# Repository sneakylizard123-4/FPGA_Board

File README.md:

# FPGA_Board

A iCE40 FPGA devboard

## Custom Features
- ICE40UP5K-SG48ITR FPGA (5280 LUTs, QFN-48)
- On-board FT232H flasher with EEPROM
- 16MB W25Q128JVS SPI flash
- USB-C with ESD protection
- RGB LED, green config-status LED, reset button
- 12MHz oscillator, 4-layer PCB

## PCB Design

The board is a 4-layer PCB.

It is built around the Lattice iCE40 FPGA, designed to be programmed over USB through the on-board FT232H. The SPI flash boots the bitstream on power-up.
It is fully supported by the open-source yosys/nextpnr/icestorm flow.

## Firmware

As the board uses an iCE40 UltraPlus, it is programmed with yosys + nextpnr-ice40 + icepack + iceprog/icestorm.

## BOM

| Ref | Value | LCSC # | MPN | Manufacturer | Footprint | Qty | Unit $ | Ext $ | Link |
|-----|-------|--------|-----|--------------|-----------|-----|--------|-------|------|
| C1,C2,C3,C4,C5,C12,C13,C14,C17,C24,C34,C35 | 10uF 0402 | C307415 | - | - | 0402 | 12 | 0.1900 | 2.28 | [LCSC](https://www.lcsc.com/product-detail/C307415.html) |
| C6,C7,C8,C9,C10,C11,C15,C16,C18,C19,C20,C21,C22,C23,C25,C26,C27,C28,C29,C30,C31,C32,C33,C37,C38 | 100nF 0402 | C131394 | - | - | 0402 | 25 | 0.0096 | 0.24 | [LCSC](https://www.lcsc.com/product-detail/C131394.html) |
| C36 | 4.7uF 0402 | C21120 | - | - | 0402 | 1 | 0.0200 | 0.02 | [LCSC](https://www.lcsc.com/product-detail/C21120.html) |
| D1 | LED_ARGB PLCC4 | C2786 | - | - | LED_Cree-PLCC4_2x2mm_CW | 1 | 0.1300 | 0.13 | [LCSC](https://www.lcsc.com/product-detail/C2786.html) |
| D2 | Green LED 0402 | C2286 | - | - | 0402 | 1 | 0.0100 | 0.01 | [LCSC](https://www.lcsc.com/product-detail/C2286.html) |
| FB1,FB2,FB3 | Ferrite Bead 1.5k | C82155 | BLM18HE152SN1D | muRata | 0603 | 3 | 0.0300 | 0.09 | [LCSC](https://www.lcsc.com/product-detail/C82155.html) |
| J1 | USB-C Receptacle 14P | C165948 | TYPE-C-31-M-12 | Korean Hroparts Elec | USB-C | 1 | 0.1900 | 0.19 | [LCSC](https://www.lcsc.com/product-detail/C165948.html) |
| J3,J4 | Pin Header 2x12 2.54mm | C492423 | PZ254V-12-12P | XFCN | Through Hole | 2 | 0.0700 | 0.14 | [LCSC](https://www.lcsc.com/product-detail/C492423.html) |
| R1,R2 | 5.1k 1% 0402 | C25905 | 0402WGF5101TCE | UNI-ROYAL | 0402 | 2 | 0.0040 | 0.01 | [LCSC](https://www.lcsc.com/product-detail/C25905.html) |
| R3,R4 | 22R 1% 0402 | C23200 | - | - | 0402 | 2 | 0.0040 | 0.01 | [LCSC](https://www.lcsc.com/product-detail/C23200.html) |
| R5,R6,R10,R11,R19,R20,R21,R23,R24 | 10k 1% 0402 | C25904 | - | - | 0402 | 9 | 0.0040 | 0.04 | [LCSC](https://www.lcsc.com/product-detail/C25904.html) |
| R7 | 1k 1% 0402 | C25898 | - | - | 0402 | 1 | 0.0040 | 0.00 | [LCSC](https://www.lcsc.com/product-detail/C25898.html) |
| R8,R9,R14 | 0R 0402 | C25887 | - | - | 0402 | 3 | 0.0030 | 0.01 | [LCSC](https://www.lcsc.com/product-detail/C25887.html) |
| R12 | 100R 1% 0402 | C22861 | - | - | 0402 | 1 | 0.0040 | 0.00 | [LCSC](https://www.lcsc.com/product-detail/C22861.html) |
| R18 | 12k 1% 0402 | C25913 | - | - | 0402 | 1 | 0.0040 | 0.00 | [LCSC](https://www.lcsc.com/product-detail/C25913.html) |
| R22 | 2.2k 1% 0402 | C25901 | - | - | 0402 | 1 | 0.0040 | 0.00 | [LCSC](https://www.lcsc.com/product-detail/C25901.html) |
| SW1 | Tactile Switch EVQPUD | C158289 | EVQPUM | PANASONIC | SMD | 1 | 0.2000 | 0.20 | [LCSC](https://www.lcsc.com/product-detail/C158289.html) |
| U1 | USBLC6-2SC6 | C7519 | USBLC6-2SC6 | ST | SOT-23-6 | 1 | 0.1800 | 0.18 | [LCSC](https://www.lcsc.com/product-detail/C7519.html) |
| U2 | TLV75712PDBV | C485515 | TLV75712PDBVR | TI | SOT-23-5 | 1 | 0.1800 | 0.18 | [LCSC](https://www.lcsc.com/product-detail/C485515.html) |
| U3 | TLV75725PDBV | C485516 | TLV75725PDBVR | TI | SOT-23-5 | 1 | 0.1800 | 0.18 | [LCSC](https://www.lcsc.com/product-detail/C485516.html) |
| U4 | TLV75733PDBV | C485517 | TLV75733PDBVR | TI | SOT-23-5 | 1 | 0.1800 | 0.18 | [LCSC](https://www.lcsc.com/product-detail/C485517.html) |
| U5 | 74AUC2G240 | C2652105 | - | - | VSSOP-8 | 1 | 0.7200 | 0.72 | [LCSC](https://www.lcsc.com/product-detail/C2652105.html) |
| U6 | ICE40UP5K-SG48ITR | C2678152 | ICE40UP5K-SG48ITR | Lattice | QFN-48 | 1 | 8.5600 | 8.56 | [LCSC](https://www.lcsc.com/product-detail/C2678152.html) |
| U7 | W25Q128JVS | C113767 | W25Q128JVS | Winbond | SOIC-8 | 1 | 2.5200 | 2.52 | [LCSC](https://www.lcsc.com/product-detail/C113767.html) |
| U8 | FT232H | C51997 | FT232HL | FTDI | LQFP-48 | 1 | 10.6200 | 10.62 | [LCSC](https://www.lcsc.com/product-detail/C51997.html) |
| U9 | 93LC56BT-I/OT | C190271 | 93LC56BT-I/OT | Microchip | SOIC-8 | 1 | 0.4500 | 0.45 | [LCSC](https://www.lcsc.com/product-detail/C190271.html) |
| Y1 | SG-210STF 12MHz | C17426037 | SG-210STF | Seiko Epson | 2.5x2.0mm | 1 | 0.3700 | 0.37 | [LCSC](https://www.lcsc.com/product-detail/C17426037.html) |
| PCB | Bare PCB | — | — | — | 50x70mm | 1 | 20.0000 | 20.00 | — |
| STENCIL | Top stencil | — | — | — | 100x150mm | 1 | 18.0000 | 18.00 | — |
| **Total** | — | — | — | — | — | **79** | — | **65.33** | — |

Full CSVs: [LCSC BOM](BOM.csv)
[KiCad generated BOM](kicad/production/bom.csv)
[Pick and place](kicad/production/positions.csv)

## Production

Production files in [Prod Files](kicad/production/)
This board assumes JLCPCB's standard 4 layer
- HASL Lead Free
- 1.6mm thick board

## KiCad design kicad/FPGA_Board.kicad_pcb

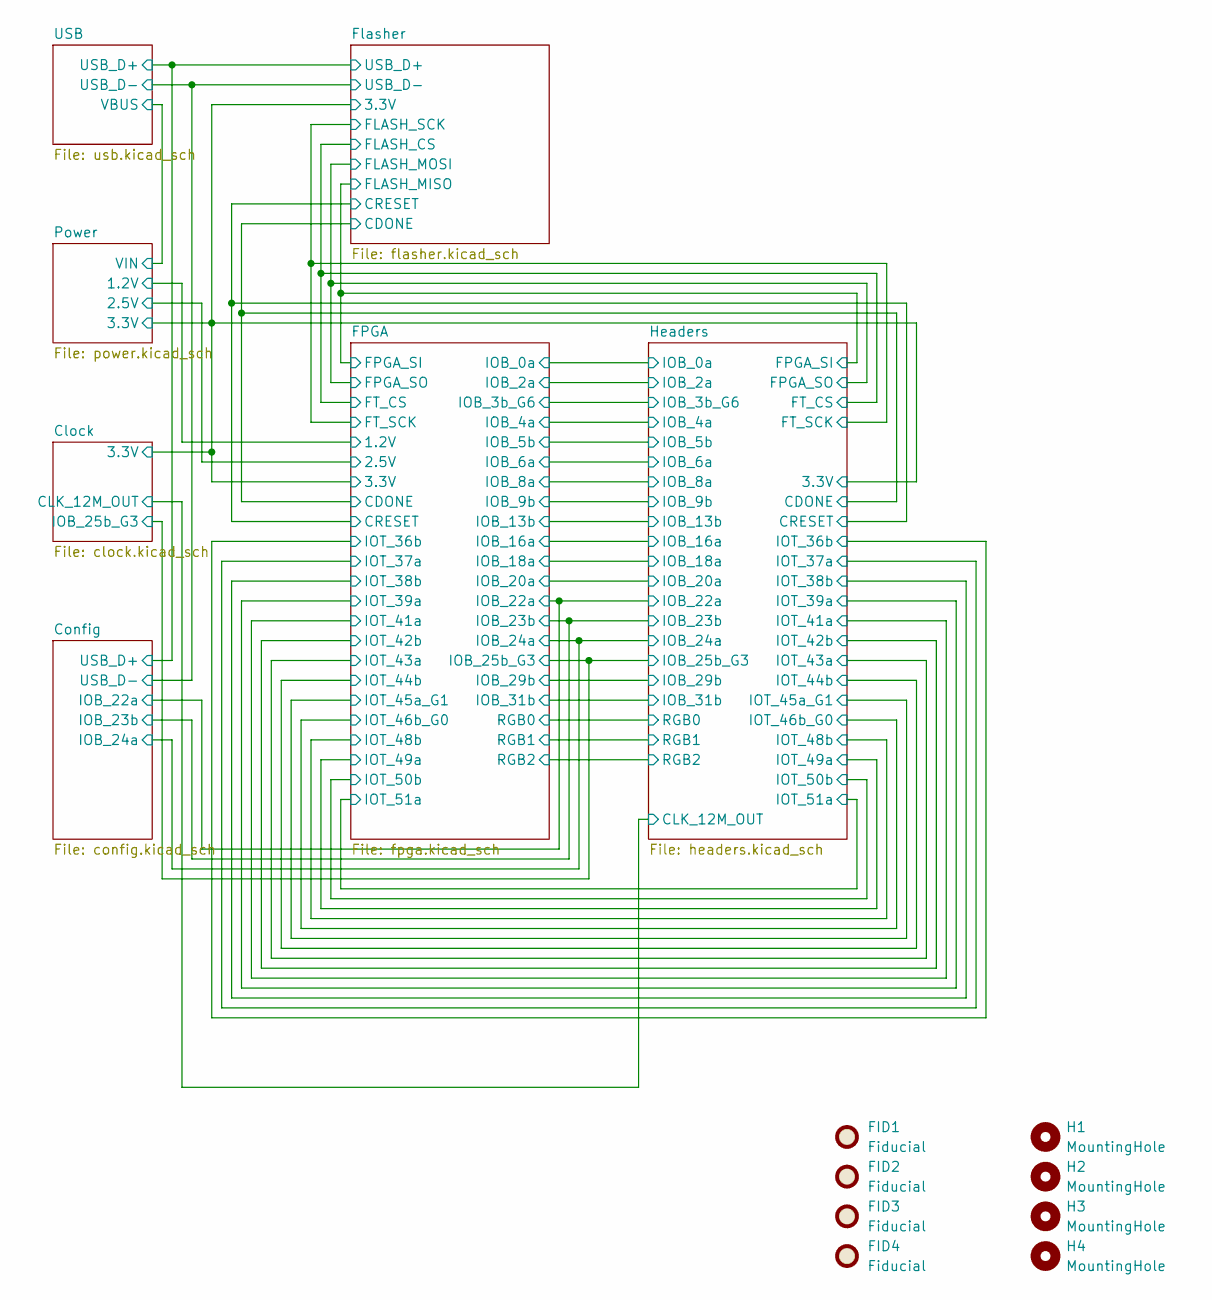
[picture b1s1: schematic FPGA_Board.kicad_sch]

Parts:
FID1, FID2, FID3, FID4: Fiducial; Fiducial_0.5mm_Mask1mm
H1, H2, H3, H4: MountingHole; MountingHole_3.2mm_M3

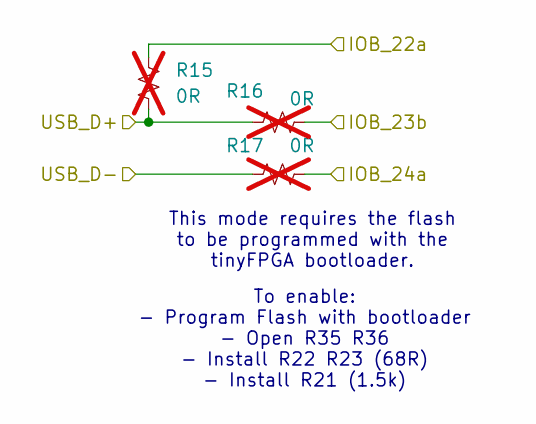
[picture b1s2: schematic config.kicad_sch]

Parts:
R15, R16, R17: 0R; R_0402_1005Metric; not fitted

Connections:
/Config/IOB_22a: R15.2; also elsewhere on the board
/Config/IOB_23b: R16.2; also elsewhere on the board
/Config/IOB_24a: R17.2; also elsewhere on the board
/Config/USB_D+: R15.1, R16.1; also elsewhere on the board
/Config/USB_D-: R17.1; also elsewhere on the board

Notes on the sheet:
This mode requires the flash to be programmed with the tinyFPGA bootloader.
To enable: - Program Flash with bootloader - Open R35 R36 - Install R22 R23 (68R) - Install R21 (1.5k)

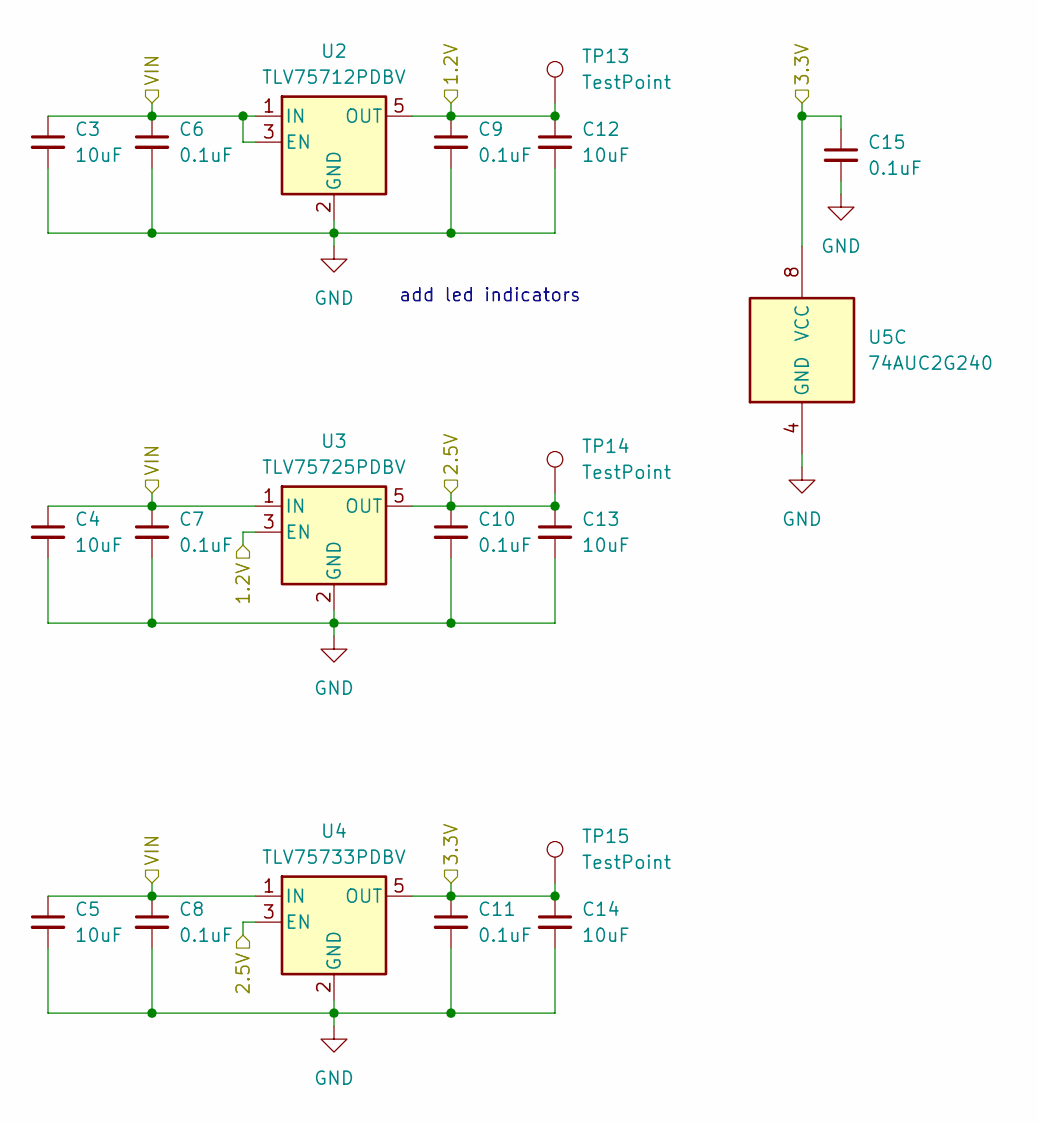
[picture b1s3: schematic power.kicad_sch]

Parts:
C3, C4, C5, C12, C13, C14: 10uF; C_0402_1005Metric
C6, C7, C8, C9, C10, C11, C15: 0.1uF; C_0402_1005Metric
TP13, TP14, TP15: TestPoint; TestPoint_Pad_2.0x2.0mm
U2: TLV75712PDBV; SOT-23-5
U3: TLV75725PDBV; SOT-23-5
U4: TLV75733PDBV; SOT-23-5
U5: 74AUC2G240; VSSOP-8_3x3mm_P0.65mm

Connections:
/FPGA/1.2V: C9.1, C12.1, TP13.1 (1_1), U2.5 (OUT), U3.3 (EN); also elsewhere on the board
/FPGA/2.5V: C10.1, C13.1, TP14.1 (1_1), U3.5 (OUT), U4.3 (EN); also elsewhere on the board
/Flasher/3.3V: C11.1, C14.1, C15.1, TP15.1 (1_1), U4.5 (OUT), U5.8 (VCC); also elsewhere on the board
/Power/VIN: C3.1, C4.1, C5.1, C6.1, C7.1, C8.1, U2.1 (IN), U2.3 (EN), U3.1 (IN), U4.1 (IN); also elsewhere on the board
GND: C3.2, C4.2, C5.2, C6.2, C7.2, C8.2, C9.2, C10.2, C11.2, C12.2, C13.2, C14.2, C15.2, U2.2 (GND), U3.2 (GND), U4.2 (GND), U5.4 (GND); also elsewhere on the board

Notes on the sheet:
add led indicators

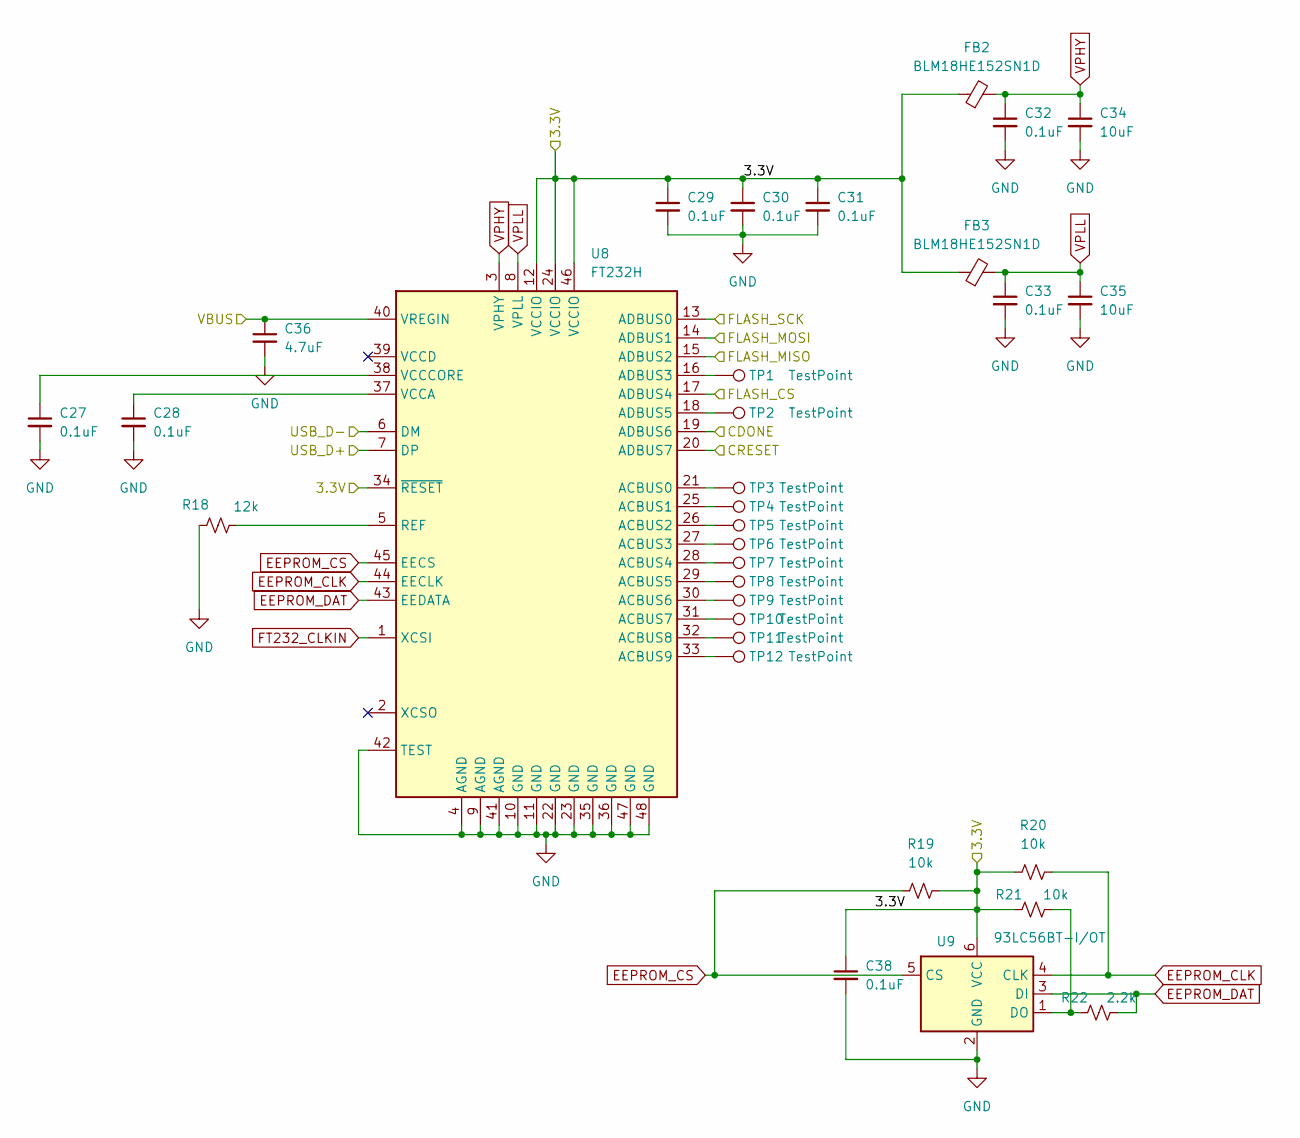
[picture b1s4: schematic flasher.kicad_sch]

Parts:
C27, C28, C29, C30, C31, C32, C33, C38: 0.1uF; C_0402_1005Metric
C34, C35: 10uF; C_0402_1005Metric
C36: 4.7uF; C_0402_1005Metric
FB2, FB3: BLM18HE152SN1D; L_0603_1608Metric
R18: 12k; R_0402_1005Metric
R19, R20, R21: 10k; R_0402_1005Metric
R22: 2.2k; R_0402_1005Metric
TP1, TP2, TP3, TP4, TP5, TP6, TP7, TP8, TP9, TP10, TP11, TP12: TestPoint; TestPoint_Pad_1.0x1.0mm
U8: FT232H; LQFP-48_7x7mm_P0.5mm
U9: 93LC56BT-I/OT; SOIC-8_3.9x4.9mm_P1.27mm

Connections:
/Config/USB_D+: U8.7 (DP); also elsewhere on the board
/Config/USB_D-: U8.6 (DM); also elsewhere on the board
/FPGA/CDONE: U8.19 (ADBUS6); also elsewhere on the board
/FPGA/CRESET: U8.20 (ADBUS7); also elsewhere on the board
/FPGA/FPGA_SI: U8.15 (ADBUS2); also elsewhere on the board
/FPGA/FPGA_SO: U8.14 (ADBUS1); also elsewhere on the board
/FPGA/FT_CS: U8.17 (ADBUS4); also elsewhere on the board
/FPGA/FT_SCK: U8.13 (ADBUS0); also elsewhere on the board
/Flasher/3.3V: C29.1, C30.1, C31.1, C38.1, FB2.1, FB3.1, R19.2, R20.1, R21.1, U8.12 (VCCIO), U8.24 (VCCIO), U8.34 (~RESET), U8.46 (VCCIO), U9.6 (VCC); also elsewhere on the board
/Flasher/VBUS: C36.1, U8.40 (VREGIN)
EEPROM_CLK: R20.2, U8.44 (EECLK), U9.4 (CLK)
EEPROM_CS: R19.1, U8.45 (EECS), U9.5 (CS)
EEPROM_DAT: R22.2, U8.43 (EEDATA), U9.3 (DI)
FT232_CLKIN: U8.1 (XCSI); also elsewhere on the board
GND: C27.2, C28.2, C29.2, C30.2, C31.2, C32.2, C33.2, C34.2, C35.2, C36.2, C38.2, R18.1, U8.4 (AGND), U8.9 (AGND), U8.10 (GND), U8.11 (GND), U8.22 (GND), U8.23 (GND), U8.35 (GND), U8.36 (GND), U8.41 (AGND), U8.42 (TEST), U8.47 (GND), U8.48 (GND), U9.2 (GND); also elsewhere on the board
unnamed: TP3.1 (1_1), U8.21 (ACBUS0)
unnamed: TP4.1 (1_1), U8.25 (ACBUS1)
unnamed: TP5.1 (1_1), U8.26 (ACBUS2)
unnamed: TP6.1 (1_1), U8.27 (ACBUS3)
unnamed: TP7.1 (1_1), U8.28 (ACBUS4)
unnamed: TP8.1 (1_1), U8.29 (ACBUS5)
unnamed: TP9.1 (1_1), U8.30 (ACBUS6)
unnamed: TP10.1 (1_1), U8.31 (ACBUS7)
unnamed: TP11.1 (1_1), U8.32 (ACBUS8)
unnamed: TP12.1 (1_1), U8.33 (ACBUS9)
unnamed: TP1.1 (1_1), U8.16 (ADBUS3)
unnamed: TP2.1 (1_1), U8.18 (ADBUS5)
unnamed: R18.2, U8.5 (REF)
unnamed: C28.1, U8.37 (VCCA)
unnamed: C27.1, U8.38 (VCCCORE)
unnamed: R21.2, R22.1, U9.1 (DO)
VPHY: C32.1, C34.1, FB2.2, U8.3 (VPHY)
VPLL: C33.1, C35.1, FB3.2, U8.8 (VPLL)

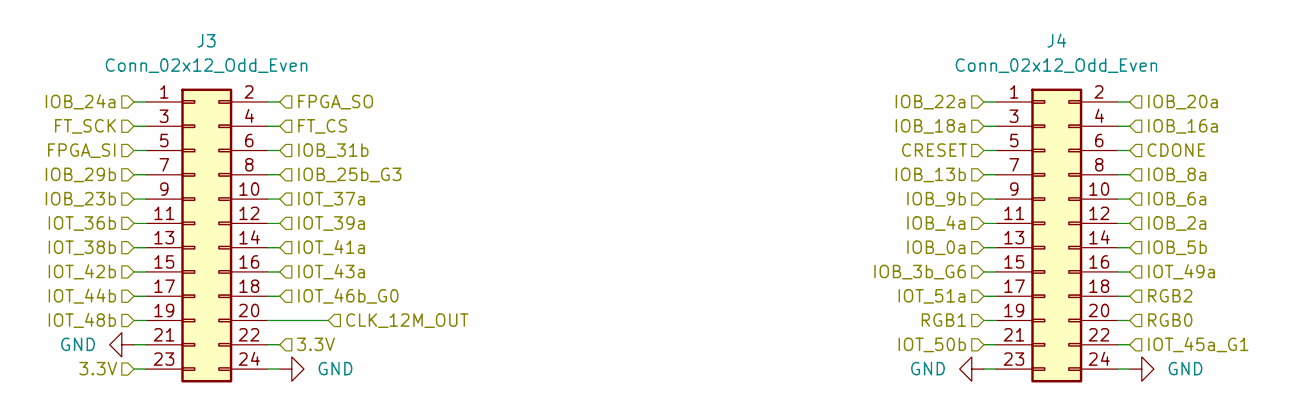
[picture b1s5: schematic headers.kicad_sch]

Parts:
J3, J4: Conn_02x12_Odd_Even; PinHeader_2x12_P2.54mm_Vertical

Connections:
/Clock/CLK_12M_OUT: J3.20; also elsewhere on the board
/Clock/IOB_25b_G3: J3.8; also elsewhere on the board
/Config/IOB_22a: J4.1; also elsewhere on the board
/Config/IOB_23b: J3.9; also elsewhere on the board
/Config/IOB_24a: J3.1; also elsewhere on the board
/FPGA/CDONE: J4.6; also elsewhere on the board
/FPGA/CRESET: J4.5; also elsewhere on the board
/FPGA/FPGA_SI: J3.5; also elsewhere on the board
/FPGA/FPGA_SO: J3.2; also elsewhere on the board
/FPGA/FT_CS: J3.4; also elsewhere on the board
/FPGA/FT_SCK: J3.3; also elsewhere on the board
/FPGA/IOB_0a: J4.13; also elsewhere on the board
/FPGA/IOB_2a: J4.12; also elsewhere on the board
/FPGA/IOB_3b_G6: J4.15; also elsewhere on the board
/FPGA/IOB_4a: J4.11; also elsewhere on the board
/FPGA/IOB_5b: J4.14; also elsewhere on the board
/FPGA/IOB_6a: J4.10; also elsewhere on the board
/FPGA/IOB_8a: J4.8; also elsewhere on the board
/FPGA/IOB_9b: J4.9; also elsewhere on the board
/FPGA/IOB_13b: J4.7; also elsewhere on the board
/FPGA/IOB_16a: J4.4; also elsewhere on the board
/FPGA/IOB_18a: J4.3; also elsewhere on the board
/FPGA/IOB_20a: J4.2; also elsewhere on the board
/FPGA/IOB_29b: J3.7; also elsewhere on the board
/FPGA/IOB_31b: J3.6; also elsewhere on the board
/FPGA/IOT_36b: J3.11; also elsewhere on the board
/FPGA/IOT_37a: J3.10; also elsewhere on the board
/FPGA/IOT_38b: J3.13; also elsewhere on the board
/FPGA/IOT_39a: J3.12; also elsewhere on the board
/FPGA/IOT_41a: J3.14; also elsewhere on the board
/FPGA/IOT_42b: J3.15; also elsewhere on the board
/FPGA/IOT_43a: J3.16; also elsewhere on the board
/FPGA/IOT_44b: J3.17; also elsewhere on the board
/FPGA/IOT_45a_G1: J4.22; also elsewhere on the board
/FPGA/IOT_46b_G0: J3.18; also elsewhere on the board
/FPGA/IOT_48b: J3.19; also elsewhere on the board
/FPGA/IOT_49a: J4.16; also elsewhere on the board
/FPGA/IOT_50b: J4.21; also elsewhere on the board
/FPGA/IOT_51a: J4.17; also elsewhere on the board
/FPGA/RGB0: J4.20; also elsewhere on the board
/FPGA/RGB1: J4.19; also elsewhere on the board
/FPGA/RGB2: J4.18; also elsewhere on the board
/Flasher/3.3V: J3.22, J3.23; also elsewhere on the board
GND: J3.21, J3.24, J4.23, J4.24; also elsewhere on the board

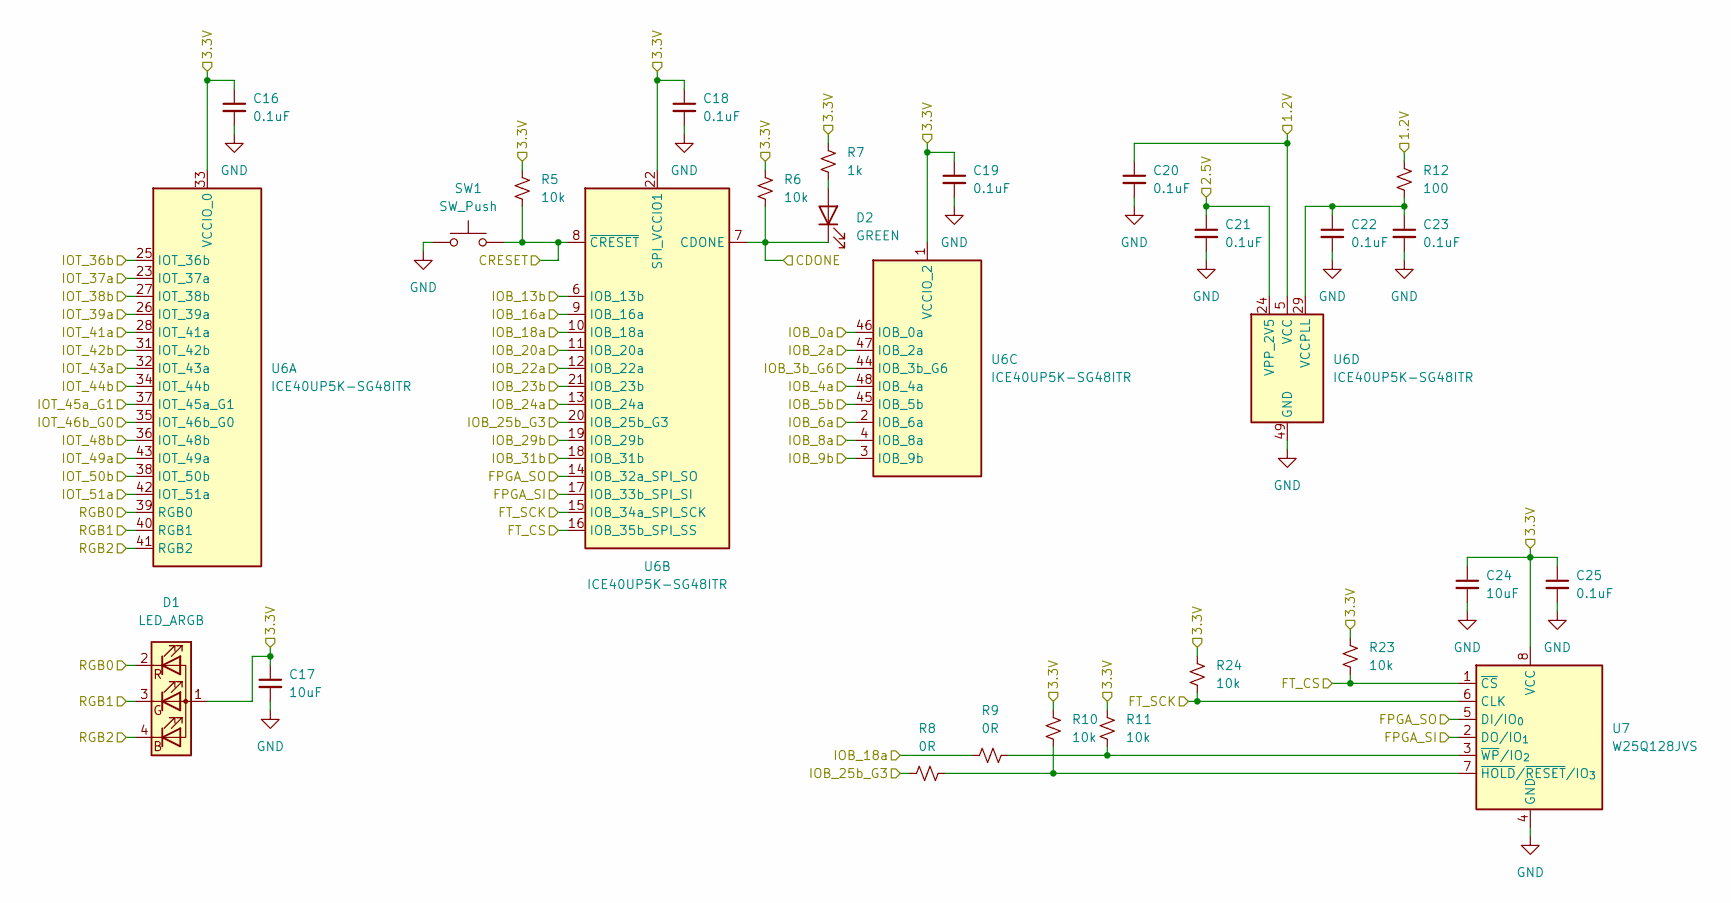
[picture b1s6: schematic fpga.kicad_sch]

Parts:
C16, C18, C19, C20, C21, C22, C23, C25: 0.1uF; C_0402_1005Metric
C17, C24: 10uF; C_0402_1005Metric
D1: LED_ARGB; LED_Cree-PLCC4_2x2mm_CW
D2: GREEN; LED_0402_1005Metric
R5, R6, R10, R11, R23, R24: 10k; R_0402_1005Metric
R7: 1k; R_0402_1005Metric
R8, R9: 0R; R_0402_1005Metric
R12: 100; R_0402_1005Metric
SW1: SW_Push; Panasonic_EVQPUM_EVQPUD
U6: ICE40UP5K-SG48ITR; QFN-48-1EP_7x7mm_P0.5mm_EP3.5x3.5mm_ThermalVias
U7: W25Q128JVS; SOIC-8_5.3x5.3mm_P1.27mm

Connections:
/Clock/IOB_25b_G3: R8.1, U6.20 (IOB_25b_G3); also elsewhere on the board
/Config/IOB_22a: U6.12 (IOB_22a); also elsewhere on the board
/Config/IOB_23b: U6.21 (IOB_23b); also elsewhere on the board
/Config/IOB_24a: U6.13 (IOB_24a); also elsewhere on the board
/FPGA/1.2V: C20.1, R12.1, U6.5 (VCC), U6.30 (VCC); also elsewhere on the board
/FPGA/2.5V: C21.1, U6.24 (VPP_2V5); also elsewhere on the board
/FPGA/CDONE: D2.1 (K), R6.2, U6.7 (CDONE); also elsewhere on the board
/FPGA/CRESET: R5.2, SW1.2, U6.8 (~CRESET); also elsewhere on the board
/FPGA/FPGA_SI: U6.17 (IOB_33b_SPI_SI), U7.2 (DO/IO_{1}); also elsewhere on the board
/FPGA/FPGA_SO: U6.14 (IOB_32a_SPI_SO), U7.5 (DI/IO_{0}); also elsewhere on the board
/FPGA/FT_CS: R23.2, U6.16 (IOB_35b_SPI_SS), U7.1 (~CS); also elsewhere on the board
/FPGA/FT_SCK: R24.2, U6.15 (IOB_34a_SPI_SCK), U7.6 (CLK); also elsewhere on the board
/FPGA/IOB_0a: U6.46 (IOB_0a); also elsewhere on the board
/FPGA/IOB_2a: U6.47 (IOB_2a); also elsewhere on the board
/FPGA/IOB_3b_G6: U6.44 (IOB_3b_G6); also elsewhere on the board
/FPGA/IOB_4a: U6.48 (IOB_4a); also elsewhere on the board
/FPGA/IOB_5b: U6.45 (IOB_5b); also elsewhere on the board
/FPGA/IOB_6a: U6.2 (IOB_6a); also elsewhere on the board
/FPGA/IOB_8a: U6.4 (IOB_8a); also elsewhere on the board
/FPGA/IOB_9b: U6.3 (IOB_9b); also elsewhere on the board
/FPGA/IOB_13b: U6.6 (IOB_13b); also elsewhere on the board
/FPGA/IOB_16a: U6.9 (IOB_16a); also elsewhere on the board
/FPGA/IOB_18a: R9.1, U6.10 (IOB_18a); also elsewhere on the board
/FPGA/IOB_20a: U6.11 (IOB_20a); also elsewhere on the board
/FPGA/IOB_29b: U6.19 (IOB_29b); also elsewhere on the board
/FPGA/IOB_31b: U6.18 (IOB_31b); also elsewhere on the board
/FPGA/IOT_36b: U6.25 (IOT_36b); also elsewhere on the board
/FPGA/IOT_37a: U6.23 (IOT_37a); also elsewhere on the board
/FPGA/IOT_38b: U6.27 (IOT_38b); also elsewhere on the board
/FPGA/IOT_39a: U6.26 (IOT_39a); also elsewhere on the board
/FPGA/IOT_41a: U6.28 (IOT_41a); also elsewhere on the board
/FPGA/IOT_42b: U6.31 (IOT_42b); also elsewhere on the board
/FPGA/IOT_43a: U6.32 (IOT_43a); also elsewhere on the board
/FPGA/IOT_44b: U6.34 (IOT_44b); also elsewhere on the board
/FPGA/IOT_45a_G1: U6.37 (IOT_45a_G1); also elsewhere on the board
/FPGA/IOT_46b_G0: U6.35 (IOT_46b_G0); also elsewhere on the board
/FPGA/IOT_48b: U6.36 (IOT_48b); also elsewhere on the board
/FPGA/IOT_49a: U6.43 (IOT_49a); also elsewhere on the board
/FPGA/IOT_50b: U6.38 (IOT_50b); also elsewhere on the board
/FPGA/IOT_51a: U6.42 (IOT_51a); also elsewhere on the board
/FPGA/RGB0: D1.2 (RK), U6.39 (RGB0); also elsewhere on the board
/FPGA/RGB1: D1.3 (GK), U6.40 (RGB1); also elsewhere on the board
/FPGA/RGB2: D1.4 (BK), U6.41 (RGB2); also elsewhere on the board
/Flasher/3.3V: C16.1, C17.1, C18.1, C19.1, C24.1, C25.1, D1.1 (A), R5.1, R6.1, R7.1, R10.1, R11.1, R23.1, R24.1, U6.1 (VCCIO_2), U6.22 (SPI_VCCIO1), U6.33 (VCCIO_0), U7.8 (VCC); also elsewhere on the board
GND: C16.2, C17.2, C18.2, C19.2, C20.2, C21.2, C22.2, C23.2, C24.2, C25.2, SW1.1, U6.49 (GND), U7.4 (GND); also elsewhere on the board
unnamed: D2.2 (A), R7.2
unnamed: C22.1, C23.1, R12.2, U6.29 (VCCPLL)
unnamed: R8.2, R10.2, U7.7 (~HOLD/~RESET/IO_{3})
unnamed: R9.2, R11.2, U7.3 (~WP/IO_{2})

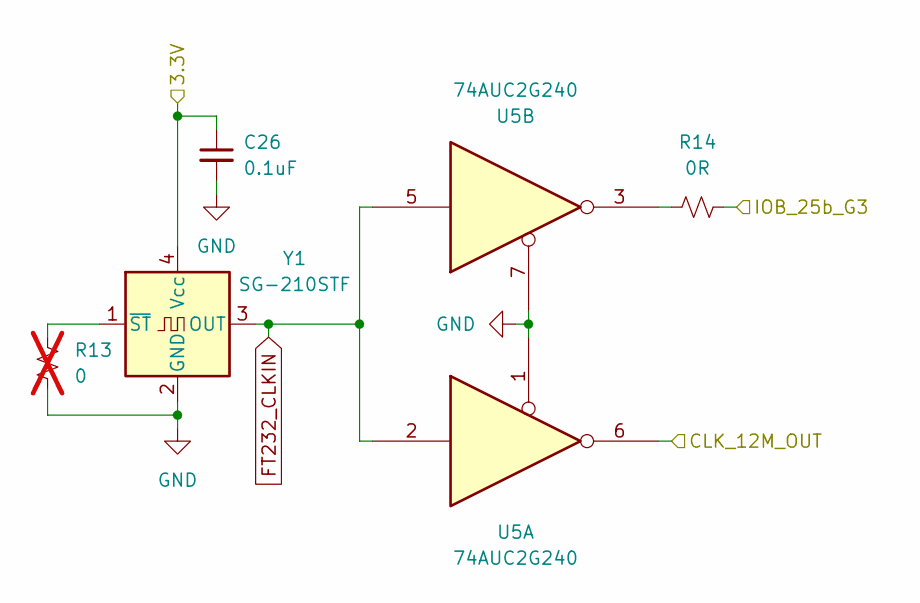
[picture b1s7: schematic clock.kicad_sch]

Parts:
C26: 0.1uF; C_0402_1005Metric
R13: 0; R_0402_1005Metric; not fitted
R14: 0R; R_0402_1005Metric
U5: 74AUC2G240; VSSOP-8_3x3mm_P0.65mm
Y1: SG-210STF; Oscillator_SMD_SeikoEpson_SG210-4Pin_2.5x2.0mm

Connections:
/Clock/CLK_12M_OUT: U5.6; also elsewhere on the board
/Clock/IOB_25b_G3: R14.2; also elsewhere on the board
/Flasher/3.3V: C26.1, Y1.4 (Vcc); also elsewhere on the board
FT232_CLKIN: U5.2, U5.5, Y1.3 (OUT); also elsewhere on the board
GND: C26.2, R13.2, U5.1, U5.7, Y1.2 (GND); also elsewhere on the board
unnamed: R14.1, U5.3
unnamed: R13.1, Y1.1 (~ST)

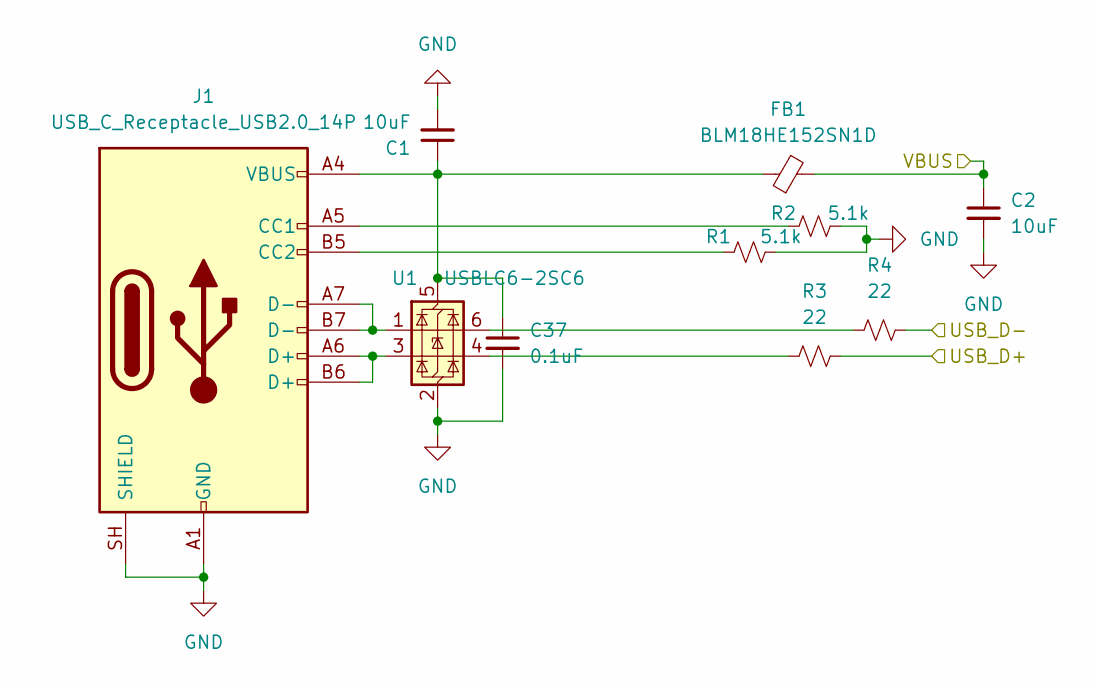
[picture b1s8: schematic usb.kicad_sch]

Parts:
C1, C2: 10uF; C_0402_1005Metric
C37: 0.1uF; C_0402_1005Metric
FB1: BLM18HE152SN1D; L_0603_1608Metric
J1: USB_C_Receptacle_USB2.0_14P; USB_C_Receptacle_HRO_TYPE-C-31-M-12
R1, R2: 5.1k; R_0402_1005Metric
R3, R4: 22; R_0402_1005Metric
U1: USBLC6-2SC6; SOT-23-6

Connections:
/Config/USB_D+: R3.1; also elsewhere on the board
/Config/USB_D-: R4.1; also elsewhere on the board
/Power/VIN: C2.1, FB1.2; also elsewhere on the board
GND: C1.2, C2.2, C37.2, J1.A1 (GND), J1.A12 (GND), J1.B1 (GND), J1.B12 (GND), J1.SH (SHIELD), R1.1, R2.1, U1.2 (GND); also elsewhere on the board
unnamed: J1.A5 (CC1), R2.2
unnamed: J1.B5 (CC2), R1.2
unnamed: J1.A6 (D+), J1.B6 (D+), U1.3 (I/O2)
unnamed: J1.A7 (D-), J1.B7 (D-), U1.1 (I/O1)
unnamed: R3.2, U1.4 (I/O2)
unnamed: R4.2, U1.6 (I/O1)
unnamed: C1.1, C37.1, FB1.1, J1.A4 (VBUS), J1.A9 (VBUS), J1.B4 (VBUS), J1.B9 (VBUS), U1.5 (VBUS)

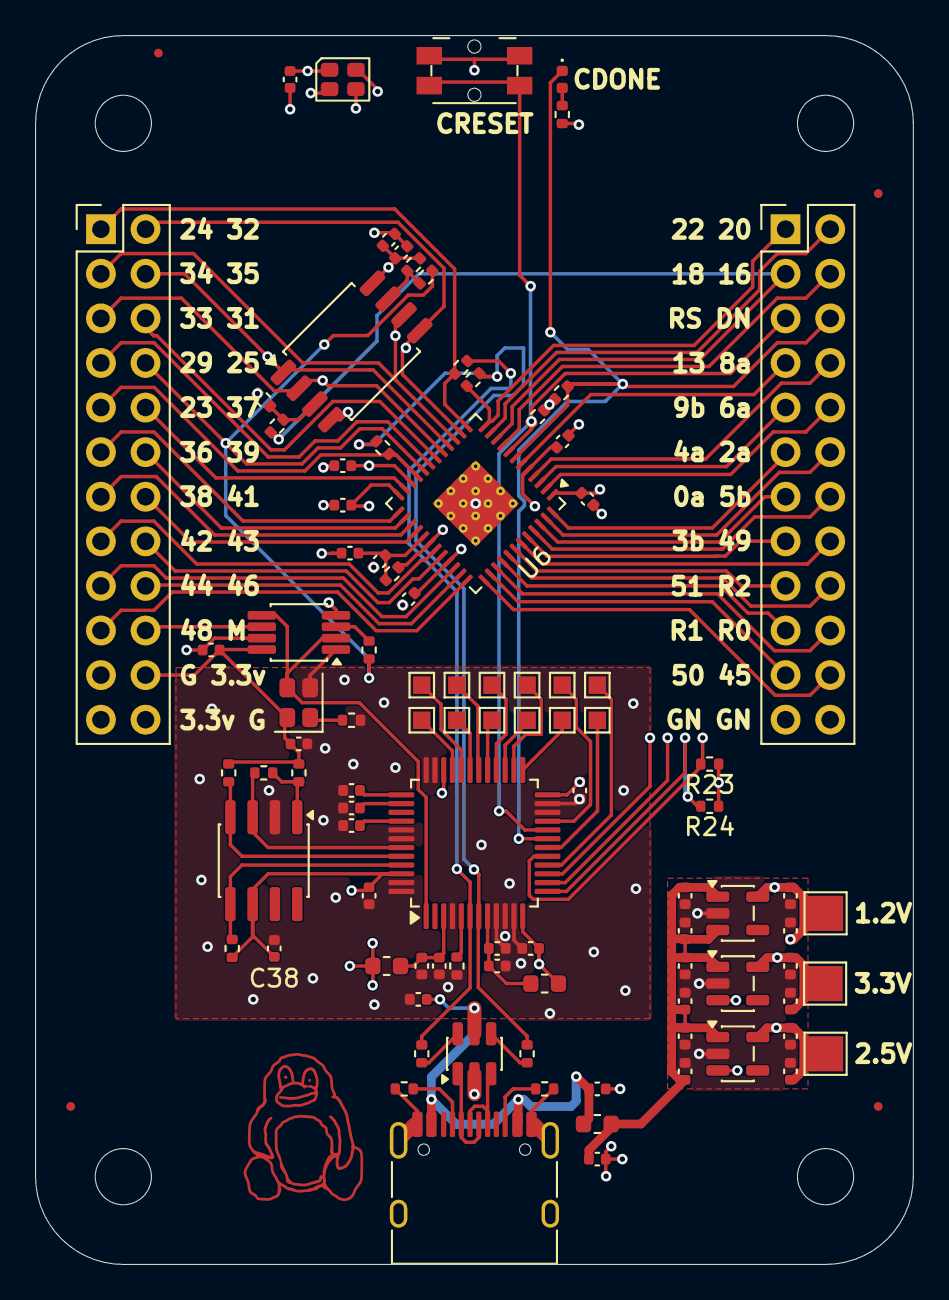
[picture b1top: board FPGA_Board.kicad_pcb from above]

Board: 4 copper layers, 50.0 x 70.0 mm, 104 parts (0 on the bottom side), 85 nets.

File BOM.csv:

Designator,Footprint,Quantity,Value,LCSC Part #,MOQ,Unit Price,Total Cost,Amount
"C1, C2, C3, C4, C5, C12, C13, C14, C17, C24, C34, C35",Capacitor_SMD:C_0402_1005Metric,12,10uF,C307415,5,$0.1900,$2.28,12
"C6, C7, C8, C9, C10, C11, C15, C16, C18, C19, C20, C21, C22, C23, C25, C26, C27, C28, C29, C30, C31, C32, C33, C37, C38",Capacitor_SMD:C_0402_1005Metric,25,0.1uF,C131394,100,$0.0096,$0.96,100
C36,Capacitor_SMD:C_0402_1005Metric,1,4.7uF,C21120,5,$0.0200,$0.10,5
D1,LED_SMD:LED_Cree-PLCC4_2x2mm_CW,1,LED_ARGB,C2786,5,$0.1300,$0.65,5
D2,LED_SMD:LED_0402_1005Metric,1,GREEN,C2286,5,$0.0100,$0.05,5
"FB1, FB2, FB3",Inductor_SMD:L_0603_1608Metric,3,BLM18HE152SN1D,C82155,10,$0.0300,$0.30,10
J1,Connector_USB:USB_C_Receptacle_HRO_TYPE-C-31-M-12,1,USB_C_Receptacle_USB2.0_14P,C165948,5,$0.1900,$0.95,5
"J3, J4",Connector_PinHeader_2.54mm:PinHeader_2x12_P2.54mm_Vertical,2,Conn_02x12_Odd_Even,C492423,10,$0.0700,$0.70,10
"R1, R2",Resistor_SMD:R_0402_1005Metric,2,5.1k,C25905,100,$0.0040,$0.40,100
"R3, R4",Resistor_SMD:R_0402_1005Metric,2,22,C23200,100,$0.0040,$0.40,100
"R5, R6, R10, R11, R19, R20, R21, R23, R24",Resistor_SMD:R_0402_1005Metric,9,10k,C25904,100,$0.0040,$0.40,100
R7,Resistor_SMD:R_0402_1005Metric,1,1k,C25898,100,$0.0040,$0.40,100
"R8, R9, R14",Resistor_SMD:R_0402_1005Metric,3,0R,C25887,100,$0.0030,$0.30,100
R12,Resistor_SMD:R_0402_1005Metric,1,100,C22861,100,$0.0040,$0.40,100
R18,Resistor_SMD:R_0402_1005Metric,1,12k,C25913,100,$0.0040,$0.40,100
R22,Resistor_SMD:R_0402_1005Metric,1,2.2k,C25901,100,$0.0040,$0.40,100
SW1,Button_Switch_SMD:Panasonic_EVQPUM_EVQPUD,1,SW_Push,C158289,1,$0.2000,$0.20,1
U1,Package_TO_SOT_SMD:SOT-23-6,1,USBLC6-2SC6,C7519,5,$0.1800,$0.90,5
U2,Package_TO_SOT_SMD:SOT-23-5,1,TLV75712PDBV,C485515,5,$0.1800,$0.90,5
U3,Package_TO_SOT_SMD:SOT-23-5,1,TLV75725PDBV,C485516,5,$0.1800,$0.90,5
U4,Package_TO_SOT_SMD:SOT-23-5,1,TLV75733PDBV,C485517,5,$0.1800,$0.90,5
U5,Package_SO:VSSOP-8_3x3mm_P0.65mm,1,74AUC2G240,C2652105,1,$0.7200,$0.72,1
U6,Package_DFN_QFN:QFN-48-1EP_7x7mm_P0.5mm_EP5.6x5.6mm,1,ICE40UP5K-SG48ITR,C2678152,1,$8.5600,$8.56,1
U7,Package_SO:SOIC-8_5.3x5.3mm_P1.27mm,1,W25Q128JVS,C113767,12,$2.5200,$30.24,12
U8,Package_QFP:LQFP-48_7x7mm_P0.5mm,1,FT232H,C51997,1,$10.6200,$10.62,1
U9,Package_SO:SOIC-8_3.9x4.9mm_P1.27mm,1,93LC56BT-I/OT,C190271,5,$0.4500,$2.25,5
Y1,Oscillator:Oscillator_SMD_SeikoEpson_SG210-4Pin_2.5x2.0mm,1,SG-210STF,C17426037,1,$0.3700,$0.37,1
PCB,,1,50x70mm Purple 1.6mm LeadFree HASL 100x150mm panel,,,,$20.00,1
STENCIL,,1,Top 100x150mm No-Framework,,,,$18.00,1

TOTAL,,,Components: $65.65,PCB: $20,Stencil: $18,GRAND TOTAL: $103.65,

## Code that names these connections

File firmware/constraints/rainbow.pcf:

# Pin constraints for the FPGA_Board (ICE40UP5K-SG48, 12 MHz reference)
# Package pin numbers confirmed from the KiCad netlist (2026-08-08).

set_io clk_12m 20    # IOB_25b_G3  - 12 MHz clock (via 74AUC2G240 buffer)
set_io rgb_r  39     # RGB0        - red   cathode (open-drain, active low)
set_io rgb_g  40     # RGB1        - green cathode (open-drain, active low)
set_io rgb_b  41     # RGB2        - blue  cathode (open-drain, active low)
